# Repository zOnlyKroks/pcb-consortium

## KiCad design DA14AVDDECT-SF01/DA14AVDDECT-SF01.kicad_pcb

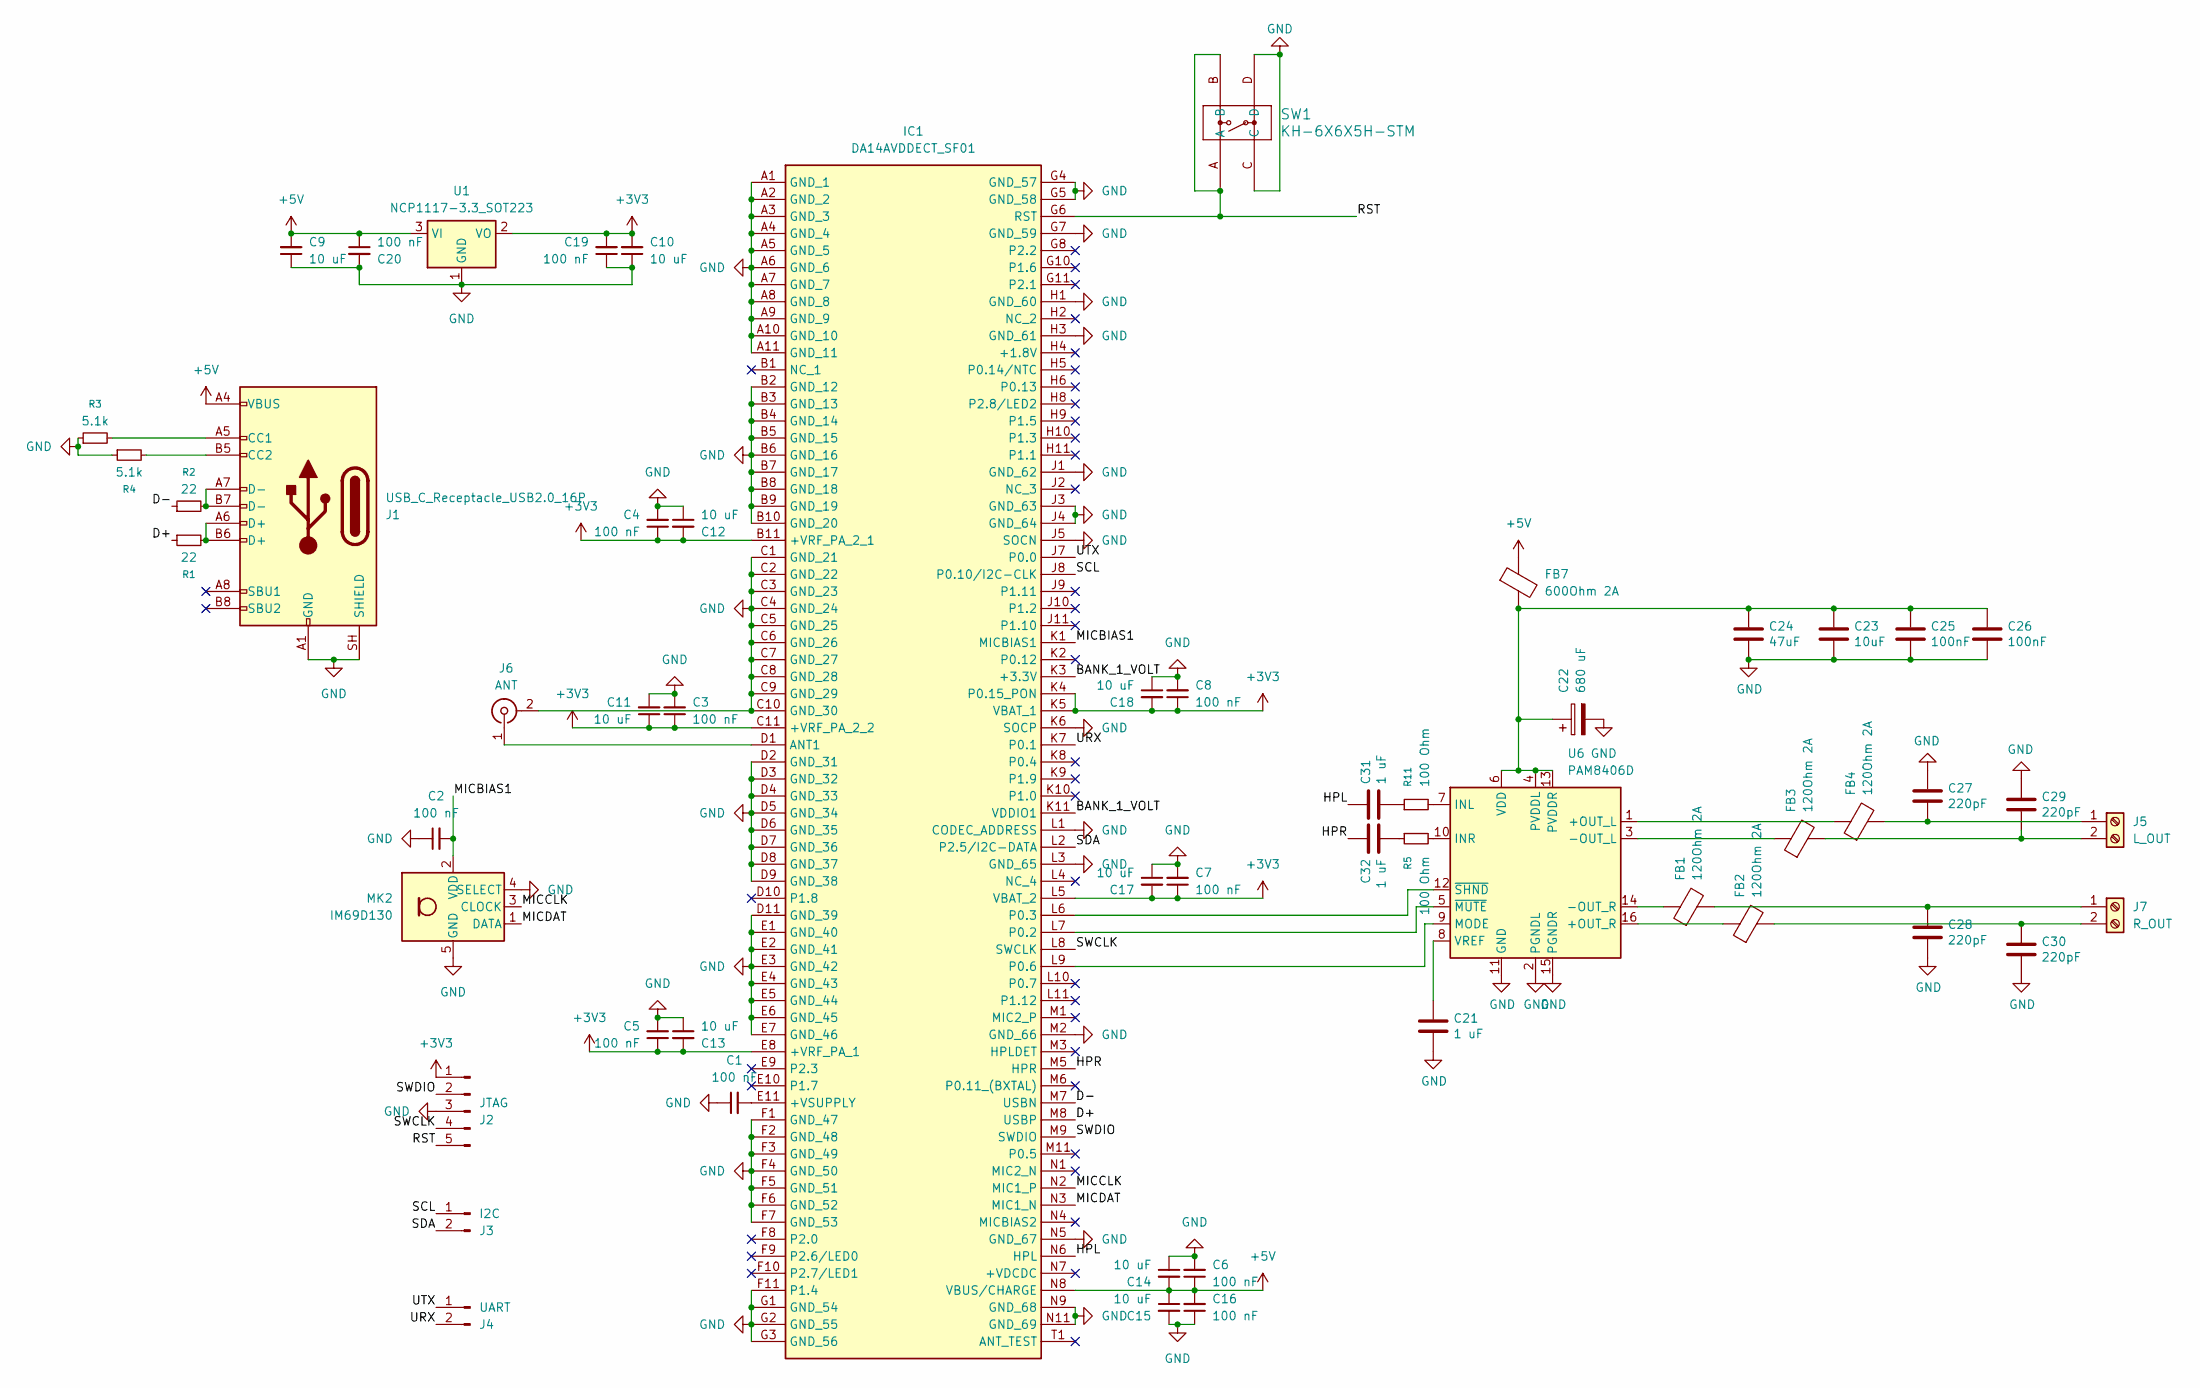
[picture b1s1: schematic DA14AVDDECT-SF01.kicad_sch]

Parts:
C1, C2, C3, C4, C5, C6, C7, C8, C16, C19, C20: 100 nF; C_0603_1608Metric
C9, C10, C11, C12, C13, C14, C15, C17, C18: 10 uF; C_0603_1608Metric
C21, C31, C32: 1 uF; C_0603_1608Metric; LCSC Part # C15849
C22: 680 uF; CP_Elec_8x10.5; LCSC Part # C970708
C23: 10uF; C_0603_1608Metric; LCSC C19702
C24: 47uF; C_1206_3216Metric; LCSC C96123
C25, C26: 100nF; C_0603_1608Metric; LCSC C14663
C27, C28, C29, C30: 220pF; C_0603_1608Metric; LCSC C1603
FB1, FB2, FB3, FB4: 120Ohm 2A; R_0805_2012Metric; LCSC Part # C356986
FB7: 600Ohm 2A; C_0603_1608Metric; LCSC Part # C780186
IC1: DA14AVDDECT_SF01; DA14AVDDECTSF01; Manufacturer_Part_Number DA14AVDDECT SF01; Mouser Part Number 724-DA14AVDDECTSF01
J1: USB_C_Receptacle_USB2.0_16P; USB_C_Receptacle_HRO_TYPE-C-31-M-12; LCSC Part # C165948
J2: JTAG; PinHeader_1x05_P2.54mm_Vertical
J3: I2C; PinHeader_1x02_P2.54mm_Vertical
J4: UART; PinHeader_1x02_P2.54mm_Vertical
J5: L_OUT; WJ500V-5.08-2P; LCSC Part # C8465
J6: ANT; SMA_BAT_Wireless_BWSMA-KWE-Z001; LCSC Part # C496551
J7: R_OUT; WJ500V-5.08-2P; LCSC Part # C8465
MK2: IM69D130; Infineon_PG-LLGA-5-1
R1, R2: 22; R_0603_1608Metric
R3, R4: 5.1k; R_0603_1608Metric
R5, R11: 100 Ohm; R_0603_1608Metric; LCSC Part # C22775
SW1: KH-6X6X5H-STM; KH-6X6X5H-STM_SKE
U1: NCP1117-3.3_SOT223; SOT-223-3_TabPin2
U6: PAM8406D; SOIC-16_3.9x9.9mm_P1.27mm; LCSC Part # C86270

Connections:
+3V3: C3.1, C4.1, C5.1, C7.1, C8.1, C10.2, C11.1, C12.2, C13.2, C17.2, C18.2, C19.2, IC1.B11 (+VRF_PA_2_1), IC1.C11 (+VRF_PA_2_2), IC1.E8 (+VRF_PA_1), IC1.K4 (P0.15_PON), IC1.K5 (VBAT_1), IC1.L5 (VBAT_2), J2.1, U1.2 (VO)
+5V: C6.1, C9.2, C14.2, C15.1, C16.2, C20.1, FB7.1, IC1.N8 (VBUS/CHARGE), J1.A4 (VBUS), J1.A9 (VBUS), J1.B4 (VBUS), J1.B9 (VBUS), U1.3 (VI)
/BANK_1_VOLT: IC1.K3 (+3.3V), IC1.K11 (VDDIO1)
/D+: IC1.M8 (USBP), R1.1
/D-: IC1.M7 (USBN), R2.1
/HPL: C31.1, IC1.N6 (HPL)
/HPR: C32.1, IC1.M5 (HPR)
/MICBIAS1: C2.2, IC1.K1 (MICBIAS1), MK2.2 (VDD)
/MICCLK: IC1.N2 (MIC1_P), MK2.3 (CLOCK)
/MICDAT: IC1.N3 (MIC1_N), MK2.1 (DATA)
/RST: IC1.G6 (RST), J2.5, SW1.A, SW1.B
/SCL: IC1.J8 (P0.10/I2C-CLK), J3.1
/SDA: IC1.L2 (P2.5/I2C-DATA), J3.2
/SWCLK: IC1.L8 (SWCLK), J2.4
/SWDIO: IC1.M9 (SWDIO), J2.2
/URX: IC1.K7 (P0.1), J4.2
/UTX: IC1.J7 (P0.0), J4.1
GND: C1.1, C2.1, C3.2, C4.2, C5.2, C6.2, C7.2, C8.2, C9.1, C10.1, C11.2, C12.1, C13.1, C14.1, C15.2, C16.1, C17.1, C18.1, C19.1, C20.2, C21.2, C22.2, C23.2, C24.2, C25.2, C26.2, C27.1, C28.2, C29.1, C30.2, IC1.A1 (GND_1), IC1.A2 (GND_2), IC1.A3 (GND_3), IC1.A4 (GND_4), IC1.A5 (GND_5), IC1.A6 (GND_6), IC1.A7 (GND_7), IC1.A8 (GND_8), IC1.A9 (GND_9), IC1.A10 (GND_10), IC1.A11 (GND_11), IC1.B2 (GND_12), IC1.B3 (GND_13), IC1.B4 (GND_14), IC1.B5 (GND_15), IC1.B6 (GND_16), IC1.B7 (GND_17), IC1.B8 (GND_18), IC1.B9 (GND_19), IC1.B10 (GND_20), IC1.C1 (GND_21), IC1.C2 (GND_22), IC1.C3 (GND_23), IC1.C4 (GND_24), IC1.C5 (GND_25), IC1.C6 (GND_26), IC1.C7 (GND_27), IC1.C8 (GND_28), IC1.C9 (GND_29), IC1.C10 (GND_30), IC1.D2 (GND_31), IC1.D3 (GND_32), IC1.D4 (GND_33), IC1.D5 (GND_34), IC1.D6 (GND_35), IC1.D7 (GND_36), IC1.D8 (GND_37), IC1.D9 (GND_38), IC1.D11 (GND_39), IC1.E1 (GND_40), IC1.E2 (GND_41), IC1.E3 (GND_42), IC1.E4 (GND_43), IC1.E5 (GND_44), IC1.E6 (GND_45), IC1.E7 (GND_46), IC1.F1 (GND_47), IC1.F2 (GND_48), IC1.F3 (GND_49), IC1.F4 (GND_50), IC1.F5 (GND_51), IC1.F6 (GND_52), IC1.F7 (GND_53), IC1.F11 (P1.4), IC1.G1 (GND_54), IC1.G2 (GND_55), IC1.G3 (GND_56), IC1.G4 (GND_57), IC1.G5 (GND_58), IC1.G7 (GND_59), IC1.H1 (GND_60), IC1.H3 (GND_61), IC1.J1 (GND_62), IC1.J3 (GND_63), IC1.J4 (GND_64), IC1.J5 (SOCN), IC1.K6 (SOCP), IC1.L1 (CODEC_ADDRESS), IC1.L3 (GND_65), IC1.M2 (GND_66), IC1.N5 (GND_67), IC1.N9 (GND_68), IC1.N11 (GND_69), J1.A1 (GND), J1.A12 (GND), J1.B1 (GND), J1.B12 (GND), J1.SH (SHIELD), J2.3, J6.2 (Ext), MK2.4 (SELECT), MK2.5 (GND), R3.1, R4.1, SW1.C, SW1.D, U1.1 (GND), U6.2 (PGNDL), U6.11 (GND), U6.15 (PGNDR)
unnamed: C31.2, R11.1
unnamed: C32.2, R5.1
unnamed: C1.2, IC1.E11 (+VSUPPLY)
unnamed: IC1.D1 (ANT1), J6.1 (In)
unnamed: IC1.L7 (P0.2), U6.5 (~MUTE)
unnamed: IC1.L6 (P0.3), U6.12 (~SHND)
unnamed: IC1.L9 (P0.6), U6.9 (MODE)
unnamed: J1.A5 (CC1), R3.2
unnamed: J1.B5 (CC2), R4.2
unnamed: J1.A6 (D+), J1.B6 (D+), R1.2
unnamed: J1.A7 (D-), J1.B7 (D-), R2.2
unnamed: C27.2, FB4.2, J5.1
unnamed: C29.2, FB3.2, J5.2
unnamed: C28.1, FB1.2, J7.1
unnamed: C30.1, FB2.2, J7.2
unnamed: FB4.1, U6.1 (+OUT_L)
unnamed: FB2.1, U6.16 (+OUT_R)
unnamed: FB3.1, U6.3 (-OUT_L)
unnamed: FB1.1, U6.14 (-OUT_R)
unnamed: R11.2, U6.7 (INL)
unnamed: R5.2, U6.10 (INR)
unnamed: C22.1, C23.1, C24.1, C25.1, C26.1, FB7.2, U6.4 (PVDDL), U6.6 (VDD), U6.13 (PVDDR)
unnamed: C21.1, U6.8 (VREF)

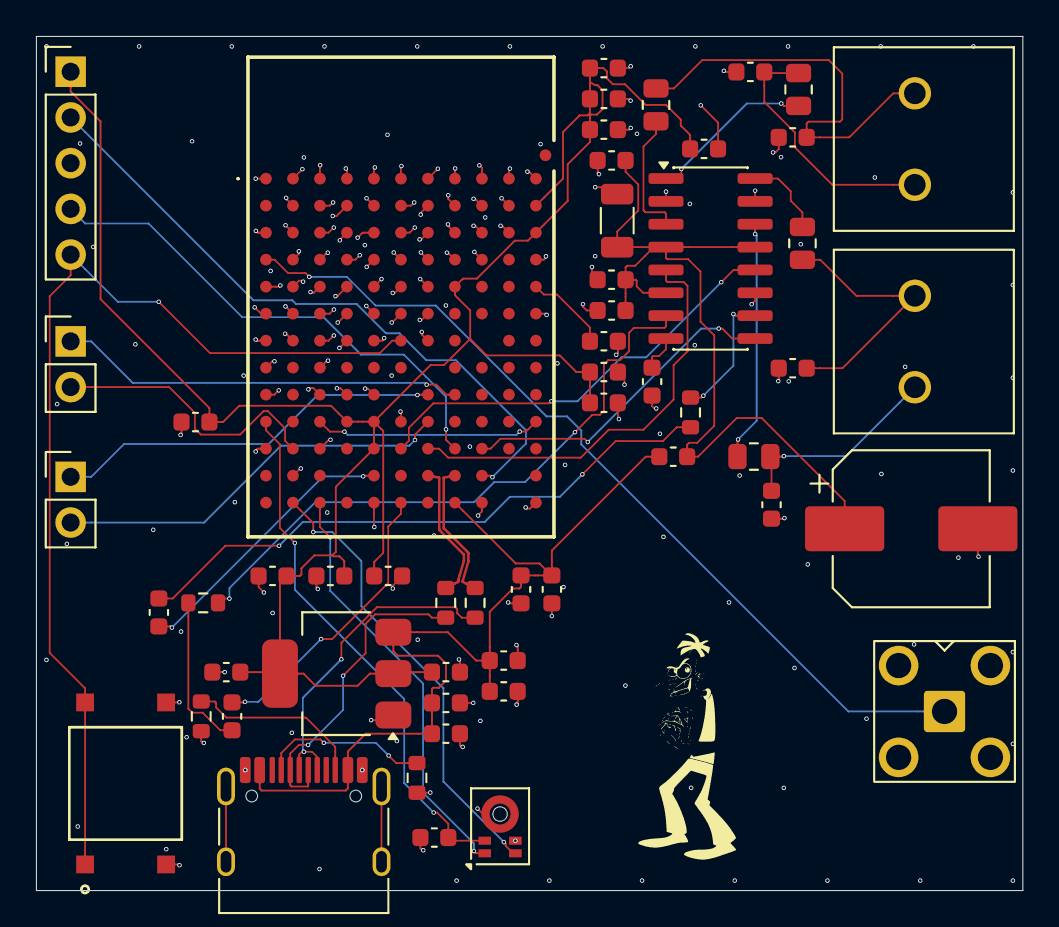
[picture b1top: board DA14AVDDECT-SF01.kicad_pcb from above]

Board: 4 copper layers, 54.8 x 47.4 mm, 55 parts (0 on the bottom side), 41 nets.

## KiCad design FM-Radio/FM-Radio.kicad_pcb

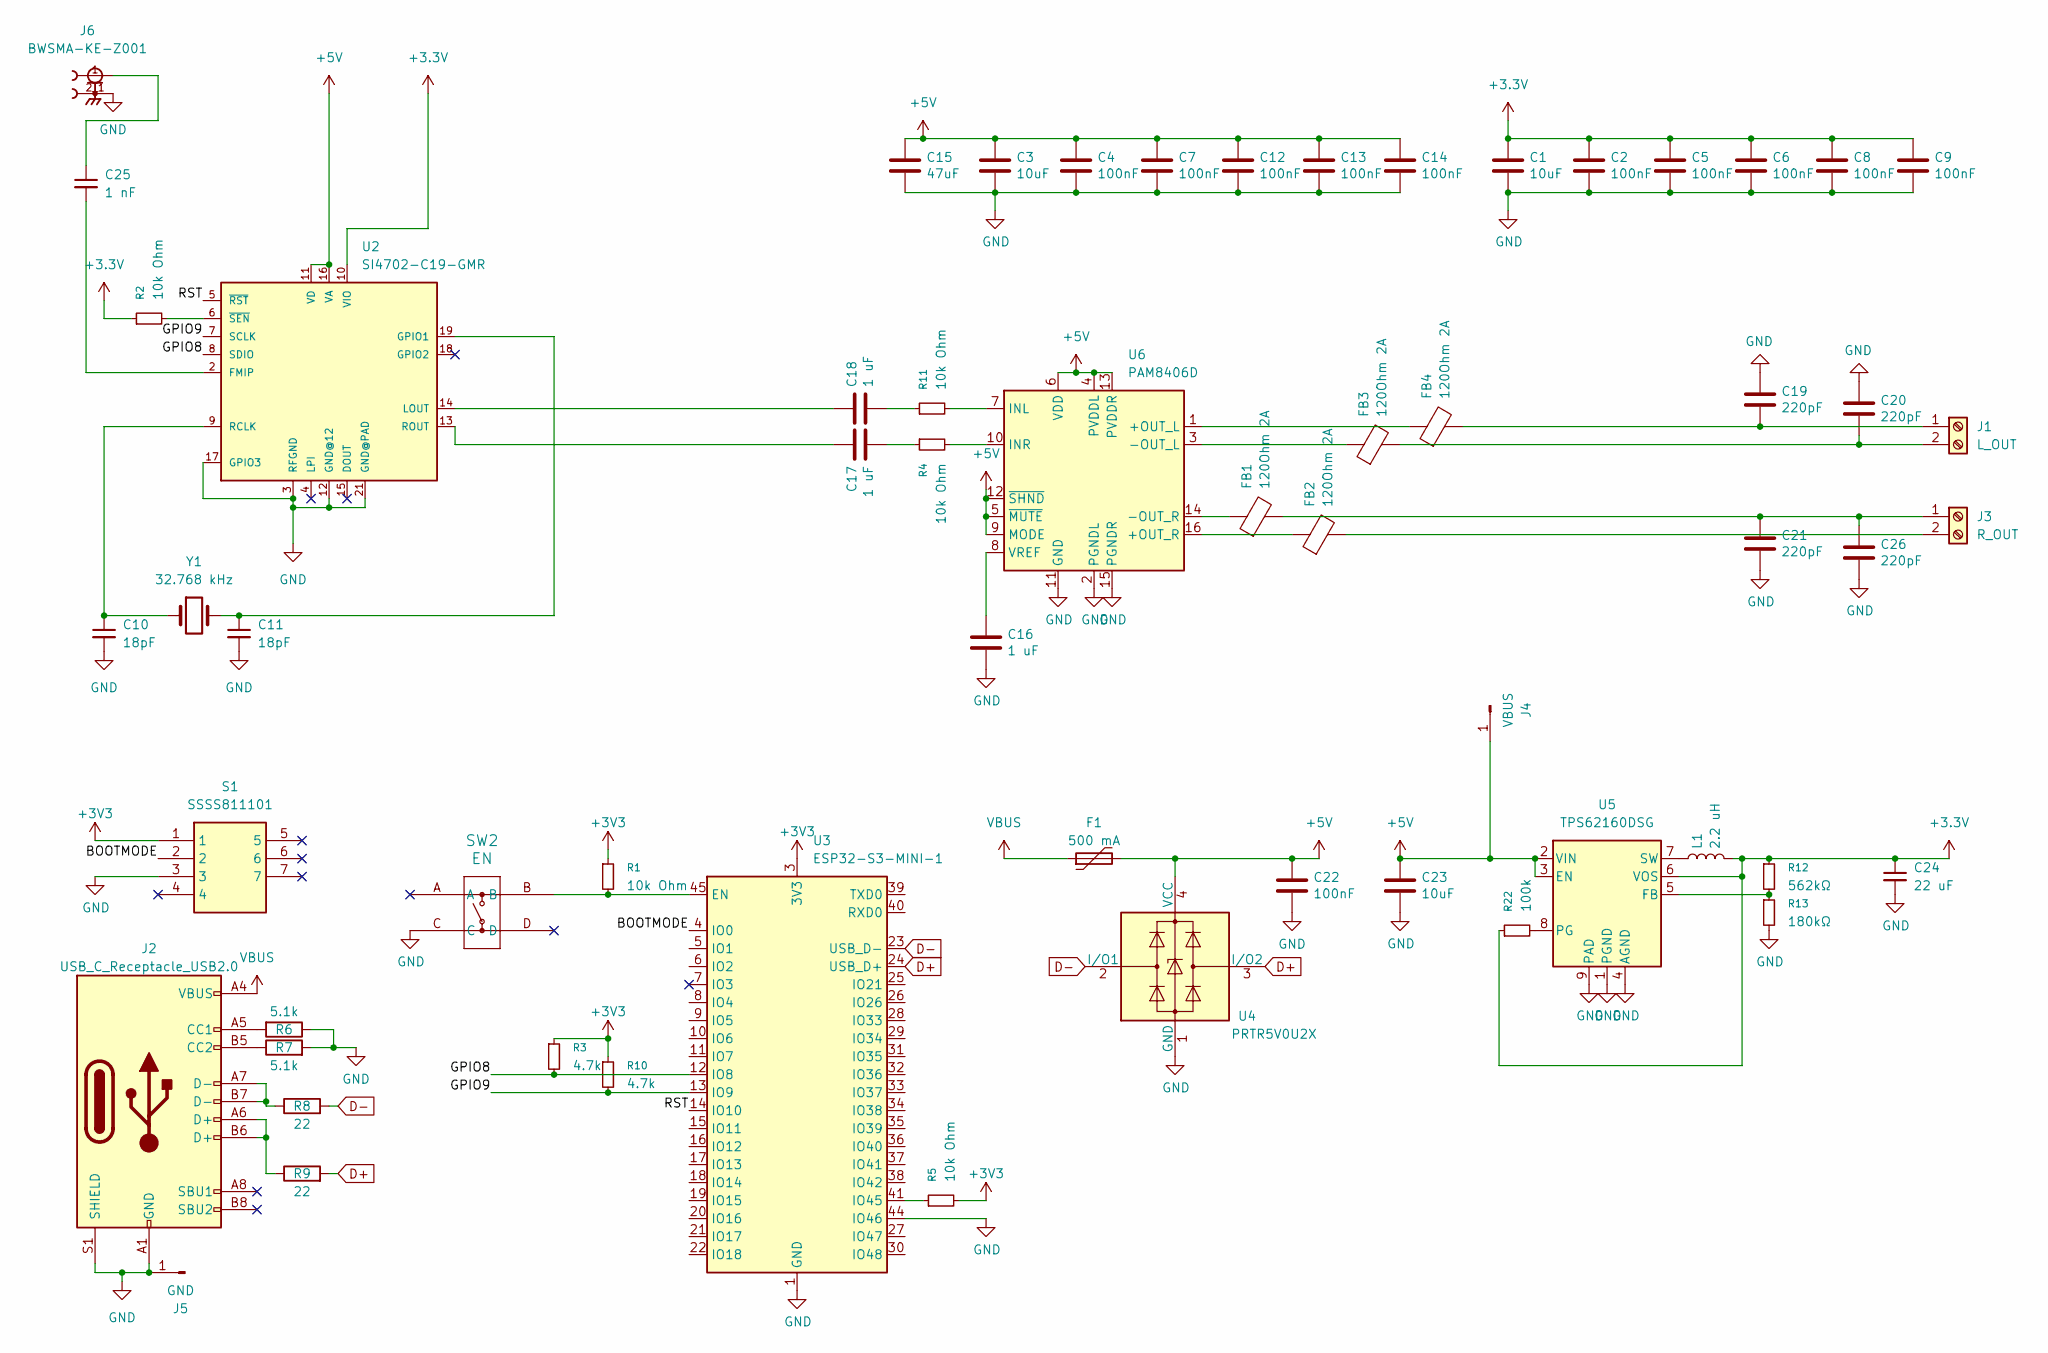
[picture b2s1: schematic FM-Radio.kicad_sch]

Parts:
C1, C3, C23: 10uF; C_0603_1608Metric; LCSC C19702
C2, C4, C5, C6, C7, C8, C9, C12, C13, C14, C22: 100nF; C_0603_1608Metric; LCSC C14663
C10, C11: 18pF; C_0603_1608Metric; LCSC Part # C1647
C15: 47uF; C_1206_3216Metric; LCSC C96123
C16, C17, C18: 1 uF; C_0603_1608Metric; LCSC Part # C29936
C19, C20, C21, C26: 220pF; C_0603_1608Metric; LCSC C1603
C24: 22 uF; C_0603_1608Metric; LCSC Part # C86295
C25: 1 nF; C_0603_1608Metric; LCSC Part # C1588
F1: 500 mA; Fuse_1206_3216Metric; LCSC C135341
FB1, FB2, FB3, FB4: 120Ohm 2A; R_0805_2012Metric; LCSC Part # C356986
J1: L_OUT; WJ500V-5.08-2P; LCSC Part # C8465
J2: USB_C_Receptacle_USB2.0; USB_C_Receptacle_HRO_TYPE-C-31-M-12; JlcRotOffset 180
J3: R_OUT; WJ500V-5.08-2P; LCSC Part # C8465
J4: VBUS; PinHeader_1x01_P2.54mm_Vertical; LCSC Part # C492400
J5: GND; PinHeader_1x01_P2.54mm_Vertical; LCSC Part # C492400
J6: BWSMA-KE-Z001; BAT_WIRELESS_BWSMA-KE-Z001; PARTREV 27/12/22; LCSC Part # C496549
L1: 2.2 uH; IND_PA4332.222NLT; LCSC Part # C3222957
R1, R2, R4, R5, R11: 10k Ohm; R_0603_1608Metric; LCSC Part # C98220
R3, R10: 4.7k; R_0603_1608Metric; LCSC Part # C99782
R6, R7: 5.1k; R_0603_1608Metric; LCSC Part # C23186
R8, R9: 22; R_0603_1608Metric; LCSC Part # C23345
R12: 562kΩ; R_0805_2012Metric; LCSC Part # C2849274
R13: 180kΩ; R_0805_2012Metric; LCSC Part # C17501
R22: 100k; R_0603_1608Metric; LCSC Part # C14675
S1: SSSS811101; Mouser Part Number 688-SSSS811101
SW2: EN; KH-6X6X5H-STM_SKE; LCSC Part # C2837531
U2: SI4702-C19-GMR; SI470X_20_QFN; MFG_PN Si4702 C19 GMR; LCSC Part # C2155666
U3: ESP32-S3-MINI-1; ESP32-S2-MINI-1; LCSC Part # C2913206
U4: PRTR5V0U2X; SOT-143; LCSC C2827688
U5: TPS62160DSG; WSON-8-1EP_2x2mm_P0.5mm_EP0.9x1.6mm_ThermalVias; LCSC Part # C324077
U6: PAM8406D; SOIC-16_3.9x9.9mm_P1.27mm; LCSC Part # C86270
Y1: 32.768 kHz; Crystal_SMD_3215-2Pin_3.2x1.5mm; LCSC Part # C32346

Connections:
+3.3V: C1.1, C2.1, C5.1, C6.1, C8.1, C9.1, C24.1, L1.2, R2.1, R12.1, R22.1, U2.10 (VIO), U5.6 (VOS)
+3V3: R1.1, R3.1, R5.2, R10.1, S1.1, U3.3 (3V3)
+5V: C3.1, C4.1, C7.1, C12.1, C13.1, C14.1, C15.1, C22.1, C23.1, F1.2, J4.1, U2.11 (VD), U2.16 (VA), U4.4 (VCC), U5.2 (VIN), U5.3 (EN), U6.4 (PVDDL), U6.5 (~MUTE), U6.6 (VDD), U6.9 (MODE), U6.12 (~SHND), U6.13 (PVDDR)
/BOOTMODE: S1.2, U3.4 (IO0)
/GPIO8: R3.2, U2.8 (SDIO), U3.12 (IO8)
/GPIO9: R10.2, U2.7 (SCLK), U3.13 (IO9)
/RST: U2.5 (~RST), U3.14 (IO10)
D+: R9.2, U3.24 (USB_D+), U4.3 (I/O2)
D-: R8.2, U3.23 (USB_D-), U4.2 (I/O1)
GND: C1.2, C2.2, C3.2, C4.2, C5.2, C6.2, C7.2, C8.2, C9.2, C10.2, C11.2, C12.2, C13.2, C14.2, C15.2, C16.2, C19.1, C20.1, C21.2, C22.2, C23.2, C24.2, C26.2, J2.A1 (GND), J2.A12 (GND), J2.B1 (GND), J2.B12 (GND), J2.S1 (SHIELD), J5.1, J6.2_1, J6.2_2, J6.2_3, J6.2_4, R6.1, R7.2, R13.2, S1.3, SW2.C, U2.3 (RFGND), U2.12 (GND@12), U2.17 (GPIO3), U2.21 (GND@PAD), U3.1 (GND), U3.2 (GND), U3.42 (GND), U3.43 (GND), U3.44 (IO46), U3.46 (GND), U3.47 (GND), U3.48 (GND), U3.49 (GND), U3.50 (GND), U3.51 (GND), U3.52 (GND), U3.53 (GND), U3.54 (GND), U3.55 (GND), U3.56 (GND), U3.57 (GND), U3.58 (GND), U3.59 (GND), U3.60 (GND), U3.61 (GND), U3.62 (GND), U3.63 (GND), U3.64 (GND), U3.65 (GND), U4.1 (GND), U5.1 (PGND), U5.4 (AGND), U5.9 (PAD), U6.2 (PGNDL), U6.11 (GND), U6.15 (PGNDR)
unnamed: C17.2, R4.1
unnamed: C18.2, R11.1
unnamed: C25.1, J6.1
unnamed: C19.2, FB4.2, J1.1
unnamed: C20.2, FB3.2, J1.2
unnamed: J2.A5 (CC1), R6.2
unnamed: J2.B5 (CC2), R7.1
unnamed: J2.A6 (D+), J2.B6 (D+), R9.1
unnamed: J2.A7 (D-), J2.B7 (D-), R8.1
unnamed: C21.1, C26.1, FB1.2, J3.1
unnamed: FB2.2, J3.2
unnamed: C25.2, U2.2 (FMIP)
unnamed: C11.1, U2.19 (GPIO1), Y1.2
unnamed: C18.1, U2.14 (LOUT)
unnamed: C10.1, U2.9 (RCLK), Y1.1
unnamed: C17.1, U2.13 (ROUT)
unnamed: R2.2, U2.6 (~SEN)
unnamed: R1.2, SW2.B, U3.45 (EN)
unnamed: R5.1, U3.41 (IO45)
unnamed: R12.2, R13.1, U5.5 (FB)
unnamed: R22.2, U5.8 (PG)
unnamed: L1.1, U5.7 (SW)
unnamed: FB4.1, U6.1 (+OUT_L)
unnamed: FB2.1, U6.16 (+OUT_R)
unnamed: FB3.1, U6.3 (-OUT_L)
unnamed: FB1.1, U6.14 (-OUT_R)
unnamed: R11.2, U6.7 (INL)
unnamed: R4.2, U6.10 (INR)
unnamed: C16.1, U6.8 (VREF)
VBUS: F1.1, J2.A4 (VBUS), J2.A9 (VBUS), J2.B4 (VBUS), J2.B9 (VBUS)

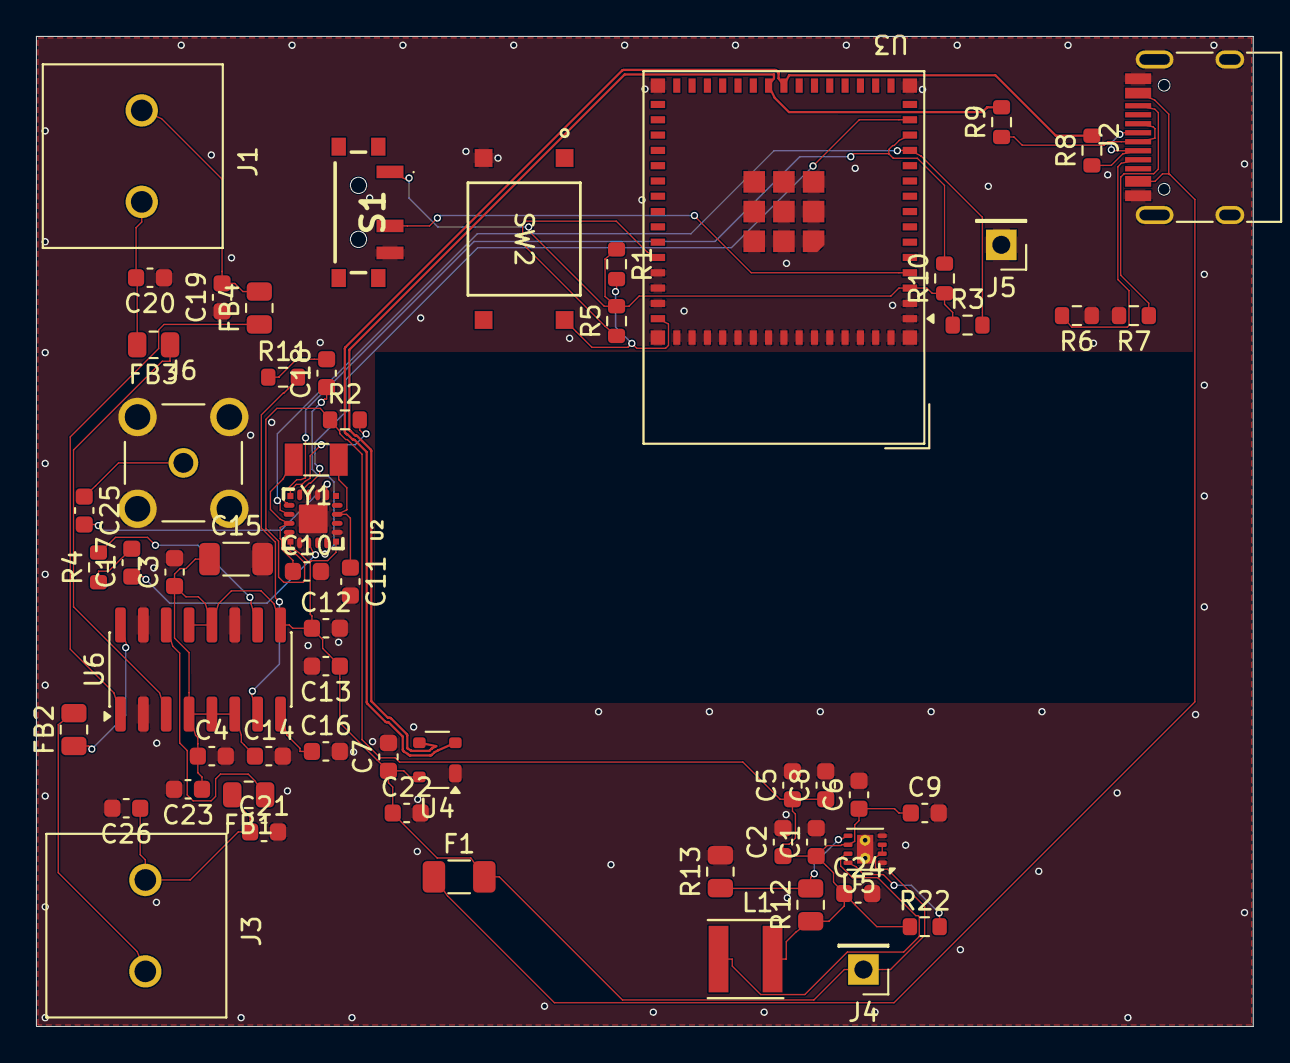
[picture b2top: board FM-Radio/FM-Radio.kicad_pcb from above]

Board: 2 copper layers, 67.6 x 55.0 mm, 60 parts (0 on the bottom side), 40 nets.

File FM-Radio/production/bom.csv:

Designator,Footprint,Quantity,Value,LCSC Part #
"C1, C3",0805,2,10uF,C440198
"C10, C11",0805,2,18pF,C113825
"C12, C13, C14, C2, C22, C4, C5, C6, C7, C8, C9",0805,11,100nF,C28233
C15,1206,1,47uF,C96123
"C16, C17, C18",0805,3,1 uF,C28323
"C19, C20, C21, C26",0805,4,220pF,C107145
C23,0805,1,10 uF,C440198
C24,0805,1,22 uF,C45783
C25,0805,1,1 nF,C46653
F1,1206,1,500 mA,C135341
"FB1, FB2, FB3, FB4",0805,4,120Ohm 2A,C356986
J1,WJ500V-5.08-2P,1,L_OUT,C8465
J2,USB_C_Receptacle_HRO_TYPE-C-31-M-12,1,USB_C_Receptacle_USB2.0,C165948
J3,WJ500V-5.08-2P,1,R_OUT,C8465
J4,PinHeader_1x01_P2.54mm_Vertical,1,VBUS,C492400
J5,PinHeader_1x01_P2.54mm_Vertical,1,GND,C492400
J6,BAT_WIRELESS_BWSMA-KE-Z001,1,BWSMA-KE-Z001,C496549
L1,IND_PA4332.222NLT,1,2.2 uH,C3222957
"R1, R11, R4, R5",0805,4,10k,C17414
"R10, R3",0805,2,4.7k,C17673
R12,0805,1,562kΩ,C2849274
R13,0805,1,180kΩ,C17501
R2,0805,1,10k Ohm,C17414
R22,0805,1,100k,C149504
"R6, R7",0805,2,5.1k,C27834
"R8, R9",0805,2,22,C17561
S1,SSSS811101,1,SSSS811101,C109335
SW2,KH-6X6X5H-STM_SKE,1,EN,C2837531 
U2,SI470X_20_QFN,1,SI4702-C19-GMR,C2155666
U3,ESP32-S2-MINI-1,1,ESP32-S3-MINI-1,C2913206 
U4,SOT-143,1,PRTR5V0U2X,C2827688
U5,WSON-8-1EP_2x2mm_P0.5mm_EP0.9x1.6mm_ThermalVias,1,TPS62160DSG,C324077 
U6,SOIC-16_3.9x9.9mm_P1.27mm,1,PAM8406D,C86270
Y1,Crystal_SMD_3215-2Pin_3.2x1.5mm,1,32.768 kHz,C32346

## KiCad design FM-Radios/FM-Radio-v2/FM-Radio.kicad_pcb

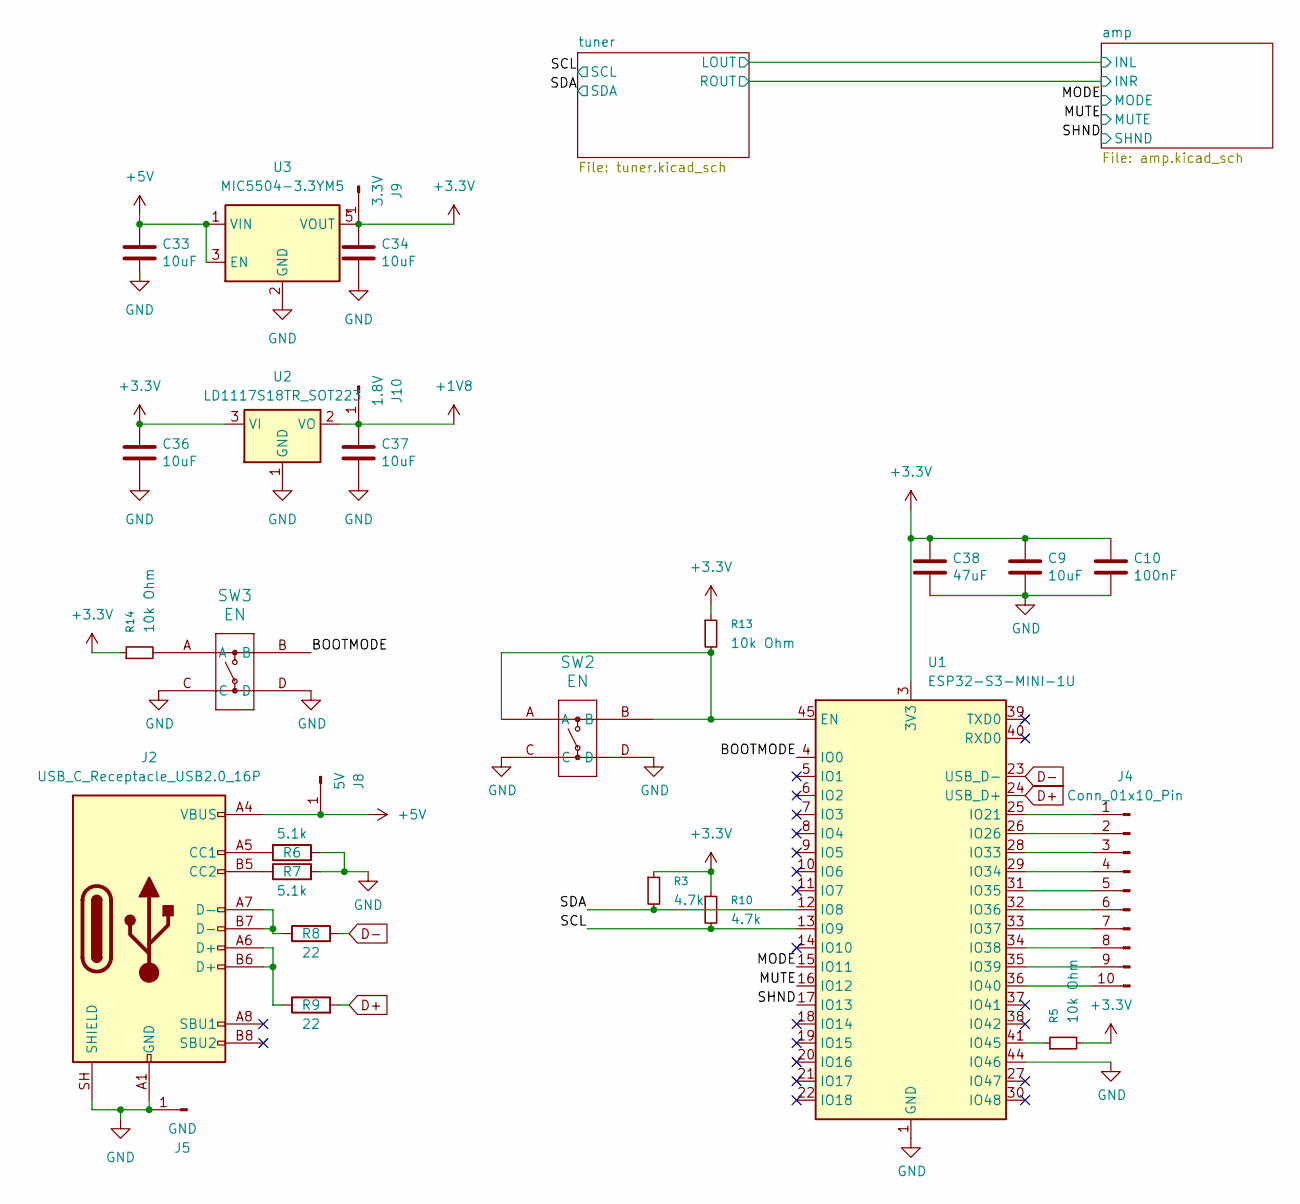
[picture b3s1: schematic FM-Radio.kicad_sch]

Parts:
C9, C33, C34, C36, C37: 10uF; C_0603_1608Metric; LCSC C19702
C10: 100nF; C_0603_1608Metric; LCSC C14663
C38: 47uF; C_1206_3216Metric; LCSC C96123
J2: USB_C_Receptacle_USB2.0_16P; USB_C_Receptacle_HRO_TYPE-C-31-M-12; LCSC Part # C165948
J4: Conn_01x10_Pin; PinHeader_1x10_P2.54mm_Vertical; LCSC Part # C492409
J5: GND; PinHeader_1x01_P2.54mm_Vertical; LCSC Part # C492400
J8: 5V; PinHeader_1x01_P2.54mm_Vertical; LCSC Part # C492400
J9: 3.3V; PinHeader_1x01_P2.54mm_Vertical; LCSC Part # C492400
J10: 1.8V; PinHeader_1x01_P2.54mm_Vertical; LCSC Part # C492400
R3, R10: 4.7k; R_0603_1608Metric; LCSC Part # C23162
R5, R13, R14: 10k Ohm; R_0603_1608Metric; LCSC Part # C25804
R6, R7: 5.1k; R_0603_1608Metric; LCSC Part # C23186
R8, R9: 22; R_0603_1608Metric; LCSC Part # C23345
SW2, SW3: EN; KH-6X6X5H-STM_SKE; LCSC Part # C2837531
U1: ESP32-S3-MINI-1U; ESP32-S2-MINI-1U; LCSC Part # C2980299
U2: LD1117S18TR_SOT223; SOT-223-3_TabPin2; LCSC Part # C80598
U3: MIC5504-3.3YM5; SOT-23-5; LCSC Part # C88419

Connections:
+1V8: C37.1, J10.1 (Pin_1_1), U2.2 (VO)
+3.3V: C9.1, C10.1, C34.1, C36.1, C38.1, J9.1 (Pin_1_1), R3.1, R5.2, R10.1, R13.1, R14.1, U1.3 (3V3), U2.3 (VI), U3.5 (VOUT); also elsewhere on the board
+5V: C33.1, J2.A4 (VBUS), J2.A9 (VBUS), J2.B4 (VBUS), J2.B9 (VBUS), J8.1 (Pin_1_1), U3.1 (VIN), U3.3 (EN); also elsewhere on the board
/BOOTMODE: SW3.B, U1.4 (IO0)
/MODE: U1.15 (IO11); also elsewhere on the board
/MUTE: U1.16 (IO12); also elsewhere on the board
/SCL: R10.2, U1.13 (IO9); also elsewhere on the board
/SDA: R3.2, U1.12 (IO8); also elsewhere on the board
/SHND: U1.17 (IO13); also elsewhere on the board
D+: R9.2, U1.24 (USB_D+)
D-: R8.2, U1.23 (USB_D-)
unnamed: J2.A5 (CC1), R6.2
unnamed: J2.B5 (CC2), R7.1
unnamed: J2.A6 (D+), J2.B6 (D+), R9.1
unnamed: J2.A7 (D-), J2.B7 (D-), R8.1
unnamed: J4.1, U1.25 (IO21)
unnamed: J4.2, U1.26 (IO26)
unnamed: J4.3, U1.28 (IO33)
unnamed: J4.4, U1.29 (IO34)
unnamed: J4.5, U1.31 (IO35)
unnamed: J4.6, U1.32 (IO36)
unnamed: J4.7, U1.33 (IO37)
unnamed: J4.8, U1.34 (IO38)
unnamed: J4.9, U1.35 (IO39)
unnamed: J4.10, U1.36 (IO40)
unnamed: R14.2, SW3.A
unnamed: R13.2, SW2.A, SW2.B, U1.45 (EN)
unnamed: R5.1, U1.41 (IO45)

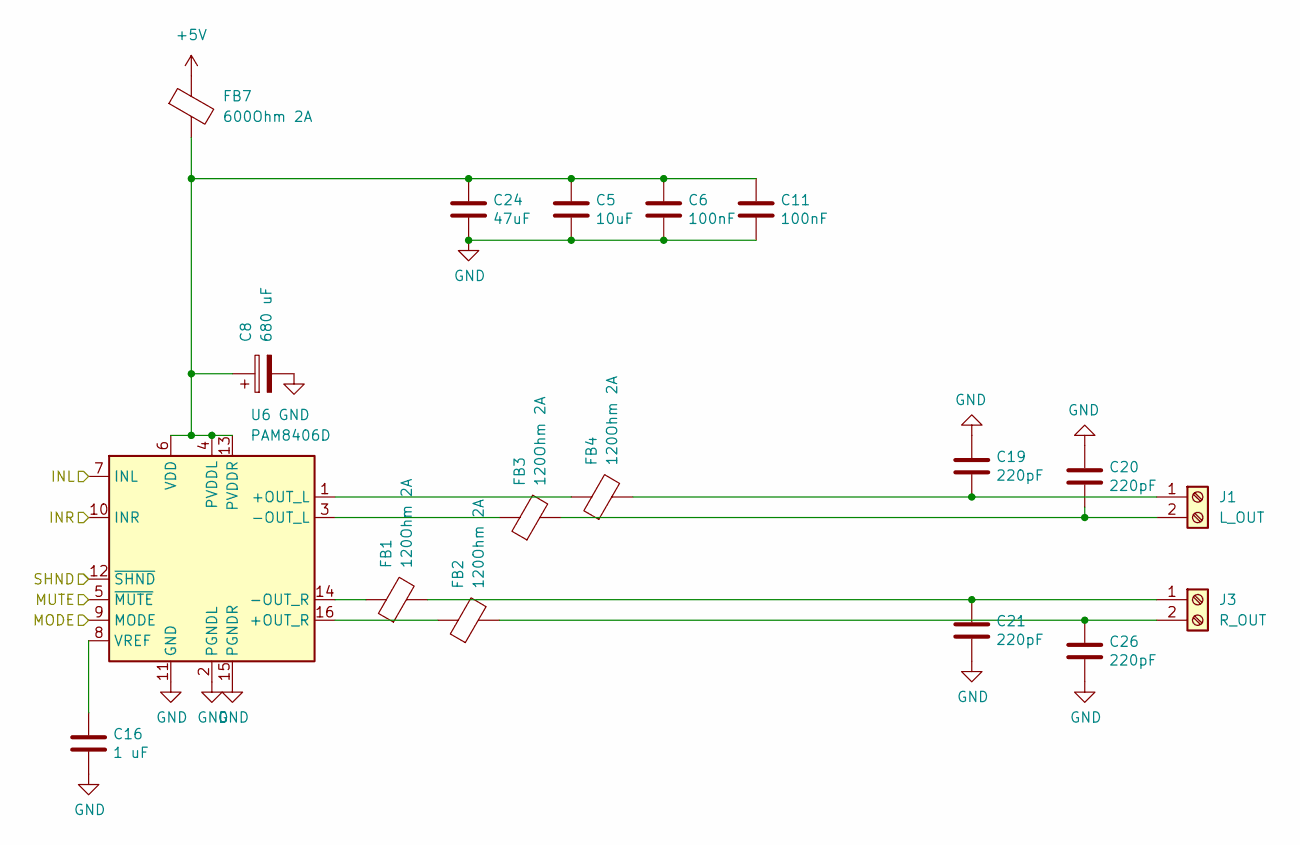
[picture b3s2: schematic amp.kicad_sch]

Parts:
C5: 10uF; C_0603_1608Metric; LCSC C19702
C6, C11: 100nF; C_0603_1608Metric; LCSC C14663
C8: 680 uF; CP_Elec_8x10.5; LCSC Part # C970708
C16: 1 uF; C_0603_1608Metric; LCSC Part # C15849
C19, C20, C21, C26: 220pF; C_0603_1608Metric; LCSC C1603
C24: 47uF; C_1206_3216Metric; LCSC C96123
FB1, FB2, FB3, FB4: 120Ohm 2A; R_0805_2012Metric; LCSC Part # C356986
FB7: 600Ohm 2A; C_0603_1608Metric; LCSC Part # C780186
J1: L_OUT; WJ500V-5.08-2P; LCSC Part # C8465
J3: R_OUT; WJ500V-5.08-2P; LCSC Part # C8465
U6: PAM8406D; SOIC-16_3.9x9.9mm_P1.27mm; LCSC Part # C86270

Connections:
+5V: FB7.1; also elsewhere on the board
/MODE: U6.9 (MODE); also elsewhere on the board
/MUTE: U6.5 (~MUTE); also elsewhere on the board
/SHND: U6.12 (~SHND); also elsewhere on the board
unnamed: C19.2, FB4.2, J1.1
unnamed: C20.2, FB3.2, J1.2
unnamed: C21.1, FB1.2, J3.1
unnamed: C26.1, FB2.2, J3.2
unnamed: FB4.1, U6.1 (+OUT_L)
unnamed: FB2.1, U6.16 (+OUT_R)
unnamed: FB3.1, U6.3 (-OUT_L)
unnamed: FB1.1, U6.14 (-OUT_R)
unnamed 52: U6.7 (INL); also elsewhere on the board
unnamed 53: U6.10 (INR); also elsewhere on the board
unnamed: C5.1, C6.1, C8.1, C11.1, C24.1, FB7.2, U6.4 (PVDDL), U6.6 (VDD), U6.13 (PVDDR)
unnamed: C16.1, U6.8 (VREF)

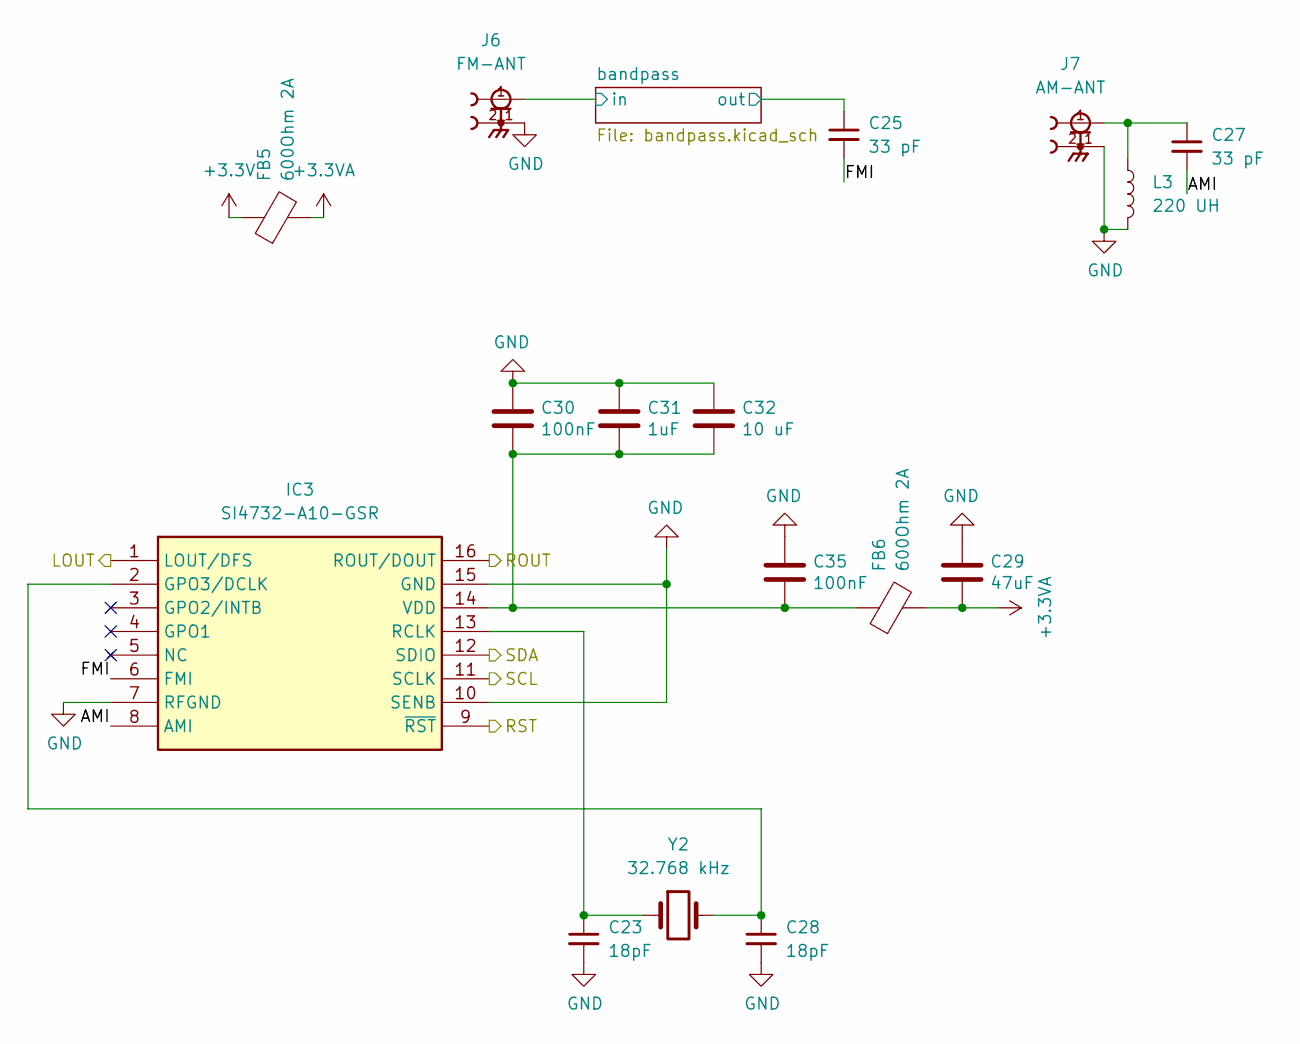
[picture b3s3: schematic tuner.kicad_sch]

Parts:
C23, C28: 18pF; C_0603_1608Metric; LCSC Part # C1647
C25, C27: 33 pF; C_0603_1608Metric; LCSC Part # C1663
C29: 47uF; C_1206_3216Metric; LCSC C96123
C30, C35: 100nF; C_0603_1608Metric; LCSC C14663
C31: 1uF; C_0603_1608Metric; LCSC C15849
C32: 10 uF; CP_EIA-3216-18_Kemet-A; LCSC C110050
FB5, FB6: 600Ohm 2A; R_0603_1608Metric; LCSC Part # C780186
IC3: SI4732-A10-GSR; SOIC127P600X175-16N; Mouser Part Number 634-SI4732-A10-GSR
J6: FM-ANT; BAT_WIRELESS_BWSMA-KE-Z001; PARTREV 27/12/22; LCSC Part # C496549
J7: AM-ANT; BAT_WIRELESS_BWSMA-KE-Z001; PARTREV 27/12/22; LCSC Part # C496549
L3: 220 UH; L_TDK_SLF6045; LCSC Part # C497842
Y2: 32.768 kHz; Crystal_SMD_3215-2Pin_3.2x1.5mm; LCSC Part # C32346

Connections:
+3.3V: FB5.1; also elsewhere on the board
/tuner/FMI: C25.2, IC3.6 (FMI); also elsewhere on the board
/tuner/bandpass/in: J6.1; also elsewhere on the board
/tuner/bandpass/out: C25.1; also elsewhere on the board
unnamed: C27.1, J7.1, L3.1
unnamed 56: C27.2, IC3.8 (AMI); also elsewhere on the board

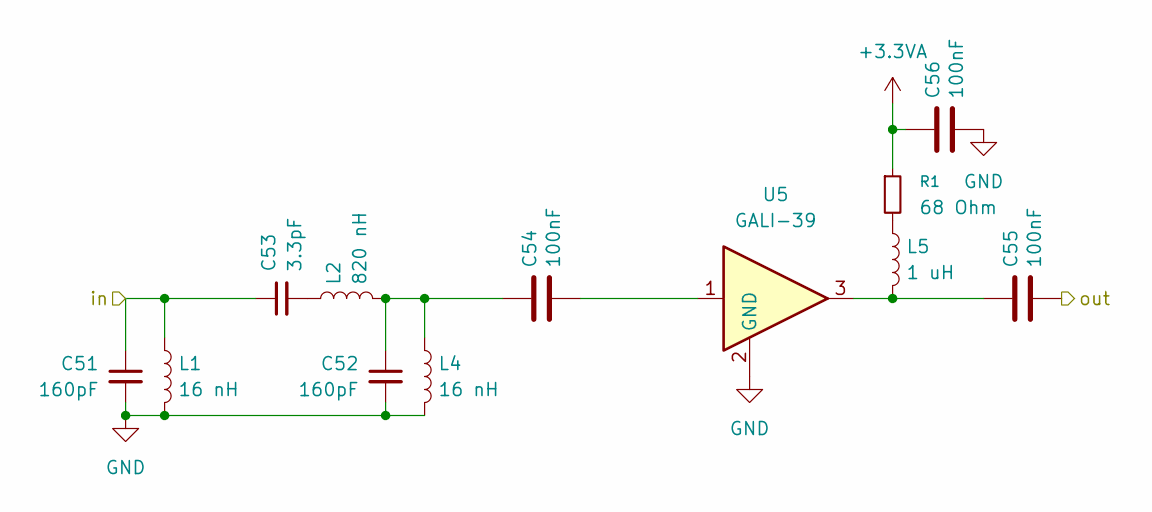
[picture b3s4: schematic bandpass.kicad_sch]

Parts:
C51, C52: 160pF; C_0603_1608Metric; LCSC Part # C22409116
C53: 3.3pF; C_0603_1608Metric; LCSC Part # C882553
C54, C55, C56: 100nF; C_0603_1608Metric; LCSC C14663
L1, L4: 16 nH; L_0805_2012Metric; LCSC Part # C19633907
L2: 820 nH; L_0805_2012Metric; LCSC Part # C162662
L5: 1 uH; L_0805_2012Metric; LCSC Part # C1331798
R1: 68 Ohm; R_0603_1608Metric; LCSC Part # C27592
U5: GALI-39; SOT-89-3

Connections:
/tuner/bandpass/in: C51.1, C53.1, L1.1; also elsewhere on the board
/tuner/bandpass/out: C55.2; also elsewhere on the board
unnamed: C52.1, C54.1, L2.2, L4.1
unnamed: C53.2, L2.1
unnamed: C54.2, U5.1
unnamed: C55.1, L5.2, U5.3
unnamed: L5.1, R1.2

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
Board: 4 copper layers, 79 parts (0 on the bottom side), 63 nets, no tracks yet.

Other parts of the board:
C12, C13: 1 uF; C_0603_1608Metric
C14: 10uF; C_0603_1608Metric
C15, C57, C58: 100nF; C_0603_1608Metric
J11: GPIOx; PinHeader_1x03_P2.54mm_Vertical
T1: H3-TC1-1-13M+; SMD_H3-TC1-1-13M
U8: TEF6686AHN/V205K; TEF6686AHNV205K
X1: SX7M9.216M20F30TNN; OSC-SMD_4P-L7.0-W5.0-BL-2

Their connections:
+3.3V: C57.2, X1.4 (Vdd); also elsewhere on the board
/SCL: U8.25 (SCL); also elsewhere on the board
/SDA: U8.24 (SDA); also elsewhere on the board
/amp/INL: C12.1, U8.30 (DAC_L)
/amp/INR: C13.1, U8.29 (DAC_R)
/tuner/FMI: T1.1; also elsewhere on the board
/tuner/FM_IN_M: T1.3, U8.5 (FM_IN_M)
/tuner/FM_IN_P: T1.5, U8.6 (FM_IN_P)
unnamed: J11.1, U8.28 (GPIO_0)
unnamed: J11.2, U8.27 (GPIO_1)
unnamed: J11.3, U8.26 (GPIO_2)
unnamed 52: C12.2; also elsewhere on the board
unnamed 53: C13.2; also elsewhere on the board
unnamed 56: U8.9 (AM_IN_P); also elsewhere on the board
unnamed: C58.2, U8.32 (XTAL_IN), X1.3 (Output)
